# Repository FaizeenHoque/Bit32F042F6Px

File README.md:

# Bit32F042F6Px

Minimal STM32F042F6Px development board. USB-C, GPIO headers, onboard 3.3V regulation. No peripherals, no bloat.

Licensed under [CERN-OHL-S v2](LICENSE).

---

## Features

- STM32F042F6Px (32KB Flash, 6KB RAM, 48MHz)
- USB-C (USB 2.0 Full Speed via PA11/PA12)
- LP5912-3.3DRV LDO — 3.3V regulated output from 5V USB
- BOOT0 and RESET buttons
- SWD header (SWDIO, SWCLK, 3.3V, GND)
- GPIO headers — all available pins broken out
- Power indicator LED

---

## Bill of Materials

| Designator | Footprint | Qty | Value |
|------------|-----------|:---:|-------|
| BOOT1, RESET1 | SW_SPST_B3U-1000P | 2 | SW_Push |
| C1 | 0402 | 1 | 0.1µF |
| C2, C4, C5 | 0402 | 3 | 1µF |
| C3 | 0402 | 1 | 10µF |
| D1 | 0402 | 1 | LED |
| J1 | USB_C_Receptacle_GCT_USB4105-xx-A_16P_TopMnt_Horizontal | 1 | USB_C_Receptacle_USB2.0_16P |
| J2, J3 | PinHeader_1x09_P2.54mm_Vertical | 2 | Conn_01x09 |
| J4 | PinHeader_1x04_P2.54mm_Vertical | 1 | Conn_01x04 |
| R1, R2 | 0402 | 2 | 10kΩ |
| R3, R4 | 0402 | 2 | 5.1kΩ |
| R5 | 0402 | 1 | 1kΩ |
| U1 | TSSOP-20_4.4x6.5mm_P0.65mm | 1 | STM32F042F6Px |
| U2 | WSON-6-1EP_2x2mm_P0.65mm_EP1x1.6mm_ThermalVias | 1 | LP5912-3.3DRV |

---

## Pinout

| Header | Pins |
|--------|------|
| J2 | +5V, +3V3 (x2), GND, GPIO\_6, GPIO\_7, GPIO\_8, GPIO\_9, GPIO\_10 |
| J3 | +5V, GND, GPIO\_0–GPIO\_5, GND |
| J4 | +3V3, SWDIO, SWCLK, GND |

---

## Schematic

---

## PCB Renders

---

## BOM
> will be added later
---

## Programming
> will be added later
---

## Repository Structure

```
Bit32F042F6Px/
├── hardware/
│   ├── Bit32F042F6Px.kicad_sch
│   ├── Bit32F042F6Px.kicad_pcb
│   └── gerbers/
├── images/
│   ├── schematic.png
│   ├── pcb_top.png
│   ├── pcb_bottom.png
│   ├── render_top.png
│   └── render_bottom.png
├── LICENSE
└── README.md
```

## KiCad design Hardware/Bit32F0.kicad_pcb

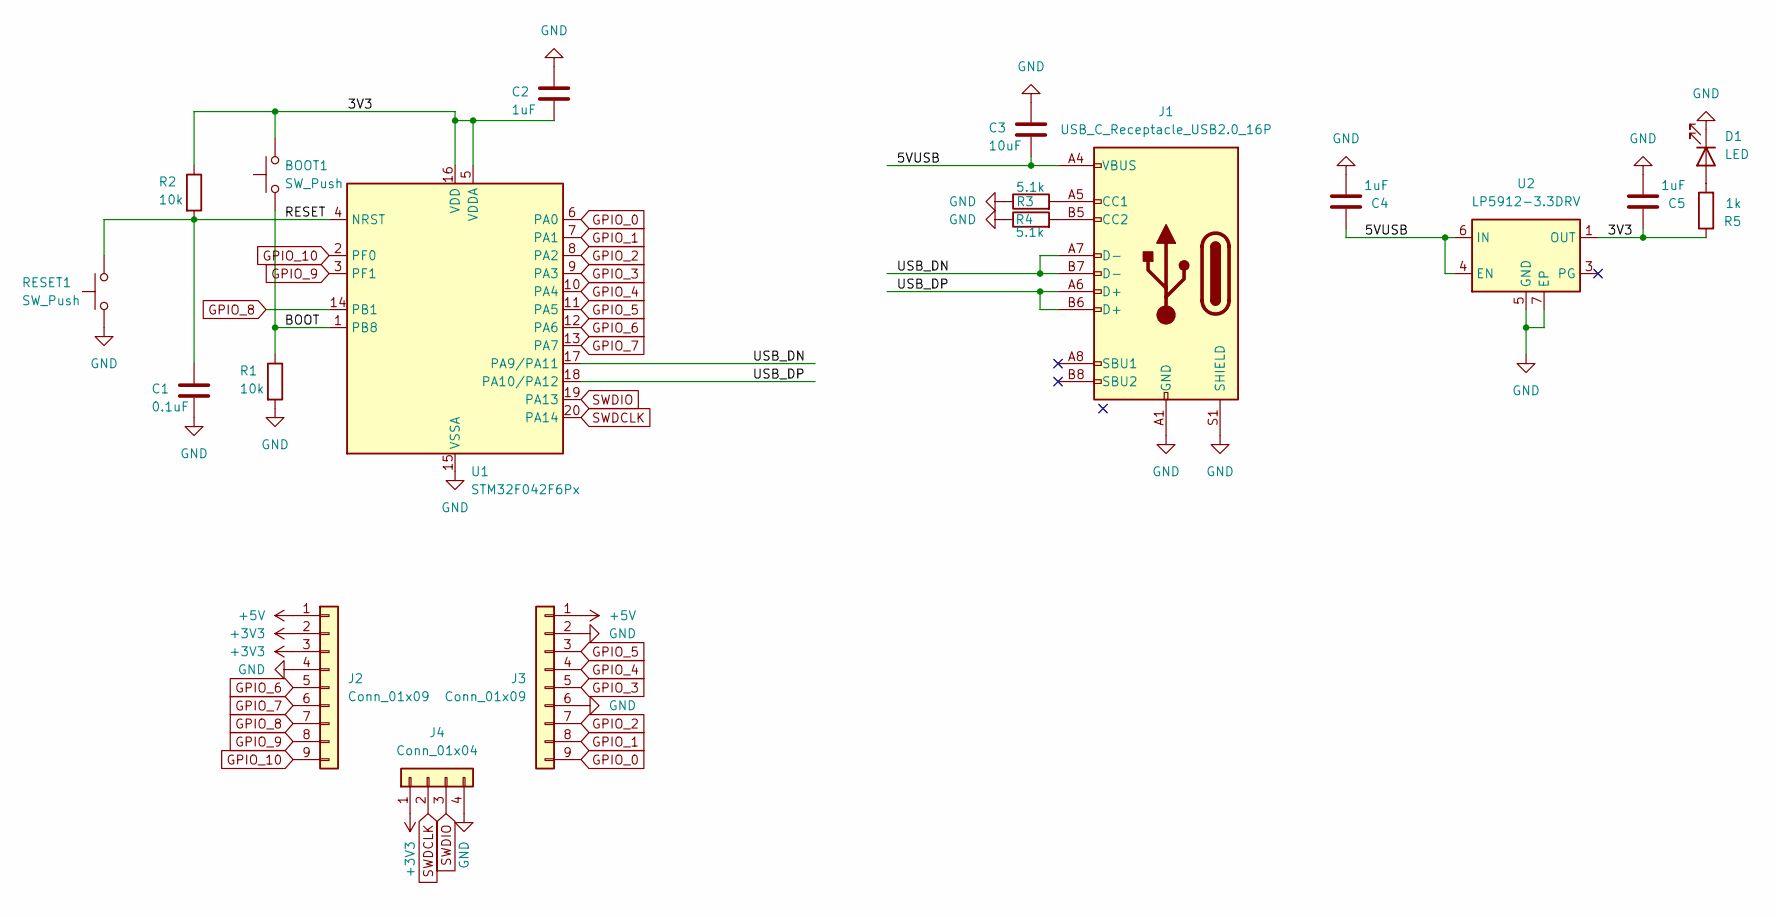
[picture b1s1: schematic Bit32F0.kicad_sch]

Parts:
BOOT1: SW_Push; SW_SPST_B3U-1000P
C1: 0.1uF; C_0402_1005Metric
C2, C4, C5: 1uF; C_0402_1005Metric
C3: 10uF; C_0402_1005Metric
D1: LED; LED_0402_1005Metric
J1: USB_C_Receptacle_USB2.0_16P; USB_C_Receptacle_GCT_USB4105-xx-A_16P_TopMnt_Horizontal
J2, J3: Conn_01x09; PinHeader_1x09_P2.54mm_Vertical
J4: Conn_01x04; PinHeader_1x04_P2.54mm_Vertical
R1, R2: 10k; R_0402_1005Metric
R3, R4: 5.1k; R_0402_1005Metric
R5: 1k; R_0402_1005Metric
RESET1: SW_Push; SW_SPST_B3U-1000P
U1: STM32F042F6Px; TSSOP-20_4.4x6.5mm_P0.65mm
U2: LP5912-3.3DRV; WSON-6-1EP_2x2mm_P0.65mm_EP1x1.6mm_ThermalVias

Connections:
+3V3: J2.2, J2.3, J4.1
+5V: J2.1, J3.1
/3V3: BOOT1.2, C2.2, C5.1, R2.1, R5.1, U1.5 (VDDA), U1.16 (VDD), U2.1 (OUT)
/5VUSB: C3.2, C4.1, J1.A4 (VBUS), J1.A9 (VBUS), J1.B4 (VBUS), J1.B9 (VBUS), U2.4 (EN), U2.6 (IN)
/BOOT: BOOT1.1, R1.1, U1.1 (PB8)
/RESET: C1.1, R2.2, RESET1.2, U1.4 (NRST)
/USB_DN: J1.A7 (D-), J1.B7 (D-), U1.17 (PA9/PA11)
/USB_DP: J1.A6 (D+), J1.B6 (D+), U1.18 (PA10/PA12)
GND: C1.2, C2.1, C3.1, C4.2, C5.2, D1.1 (K), J1.A1 (GND), J1.A12 (GND), J1.B1 (GND), J1.B12 (GND), J1.S1 (SHIELD), J2.4, J3.2, J3.6, J4.4, R1.2, R3.1, R4.1, RESET1.1, U1.15 (VSSA), U2.5 (GND), U2.7 (EP)
GPIO_0: J3.9, U1.6 (PA0)
GPIO_1: J3.8, U1.7 (PA1)
GPIO_2: J3.7, U1.8 (PA2)
GPIO_3: J3.5, U1.9 (PA3)
GPIO_4: J3.4, U1.10 (PA4)
GPIO_5: J3.3, U1.11 (PA5)
GPIO_6: J2.5, U1.12 (PA6)
GPIO_7: J2.6, U1.13 (PA7)
GPIO_8: J2.7, U1.14 (PB1)
GPIO_9: J2.8, U1.3 (PF1)
GPIO_10: J2.9, U1.2 (PF0)
unnamed: D1.2 (A), R5.2
unnamed: J1.A5 (CC1), R3.2
unnamed: J1.B5 (CC2), R4.2
SWDCLK: J4.2, U1.20 (PA14)
SWDIO: J4.3, U1.19 (PA13)

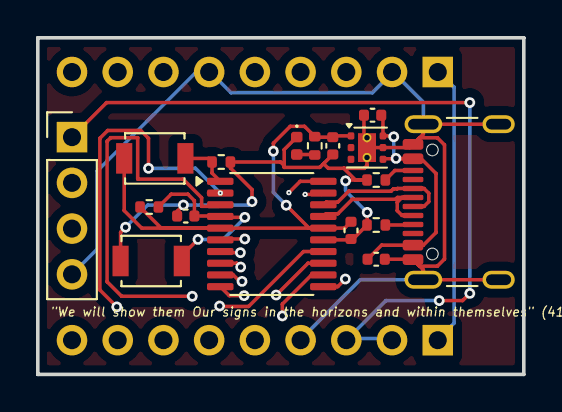
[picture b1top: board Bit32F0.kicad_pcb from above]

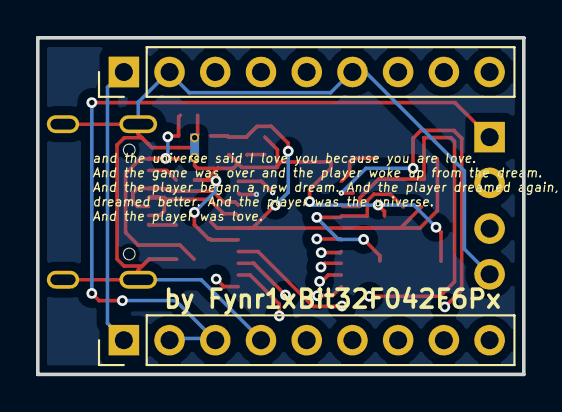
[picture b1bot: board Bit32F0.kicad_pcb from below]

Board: 4 copper layers, 27.0 x 18.7 mm, 19 parts (2 on the bottom side), 25 nets.

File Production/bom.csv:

Designator,Footprint,Quantity,Value,LCSC Part #
"BOOT1, RESET1",SW_SPST_B3U-1000P,2,SW_Push,
C1,0402,1,0.1uF,
"C2, C4, C5",0402,3,1uF,
C3,0402,1,10uF,
D1,0402,1,LED,
J1,USB_C_Receptacle_GCT_USB4105-xx-A_16P_TopMnt_Horizontal,1,USB_C_Receptacle_USB2.0_16P,
"J2, J3",PinHeader_1x09_P2.54mm_Vertical,2,Conn_01x09,
J4,PinHeader_1x04_P2.54mm_Vertical,1,Conn_01x04,
"R1, R2",0402,2,10k,
"R3, R4",0402,2,5.1k,
R5,0402,1,1k,
U1,TSSOP-20_4.4x6.5mm_P0.65mm,1,STM32F042F6Px,
U2,WSON-6-1EP_2x2mm_P0.65mm_EP1x1.6mm_ThermalVias,1,LP5912-3.3DRV,

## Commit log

2026-03-16 Create LICENSE
2026-03-16 Added Hardware files
2026-03-16 Added pictures
2026-03-16 Fix image paths in README.md
    Updated image paths in README to use capital 'I' for 'Images'.
2026-03-16 Update PCB section and remove render images
    Renamed section from 'Render' to 'PCB Renders' and removed render images.
2026-03-16 Add production files
2026-04-01 Update BOM entries in bom.csv
    Removed BOM entries and added new entries with the same format.
2026-04-01 Fix formatting issues in bom.csv
2026-04-01 Add Bill of Materials to README
    Added a Bill of Materials section with component details.
2026-04-01 Add main Arduino sketch for LED control
    Initialize USB serial communication and control an LED.
